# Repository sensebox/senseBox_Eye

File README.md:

# senseBox Eye
## /examples
Some basic examples to test functionality of the MCU. If youre interested in the AI capabilities of the board you can check out this [image classifier](https://github.com/PaulaScharf/senseBox_Eye-edge_impulse) that I created using edge-impulse.

## /hardware
Contains datasheets and schematics.

## /BSP
Contains configuration for the board support package (which have to be included into the [Arduino core for the ESP32](https://github.com/espressif/arduino-esp32)), UF2 bootloader and circuit python bootloader.

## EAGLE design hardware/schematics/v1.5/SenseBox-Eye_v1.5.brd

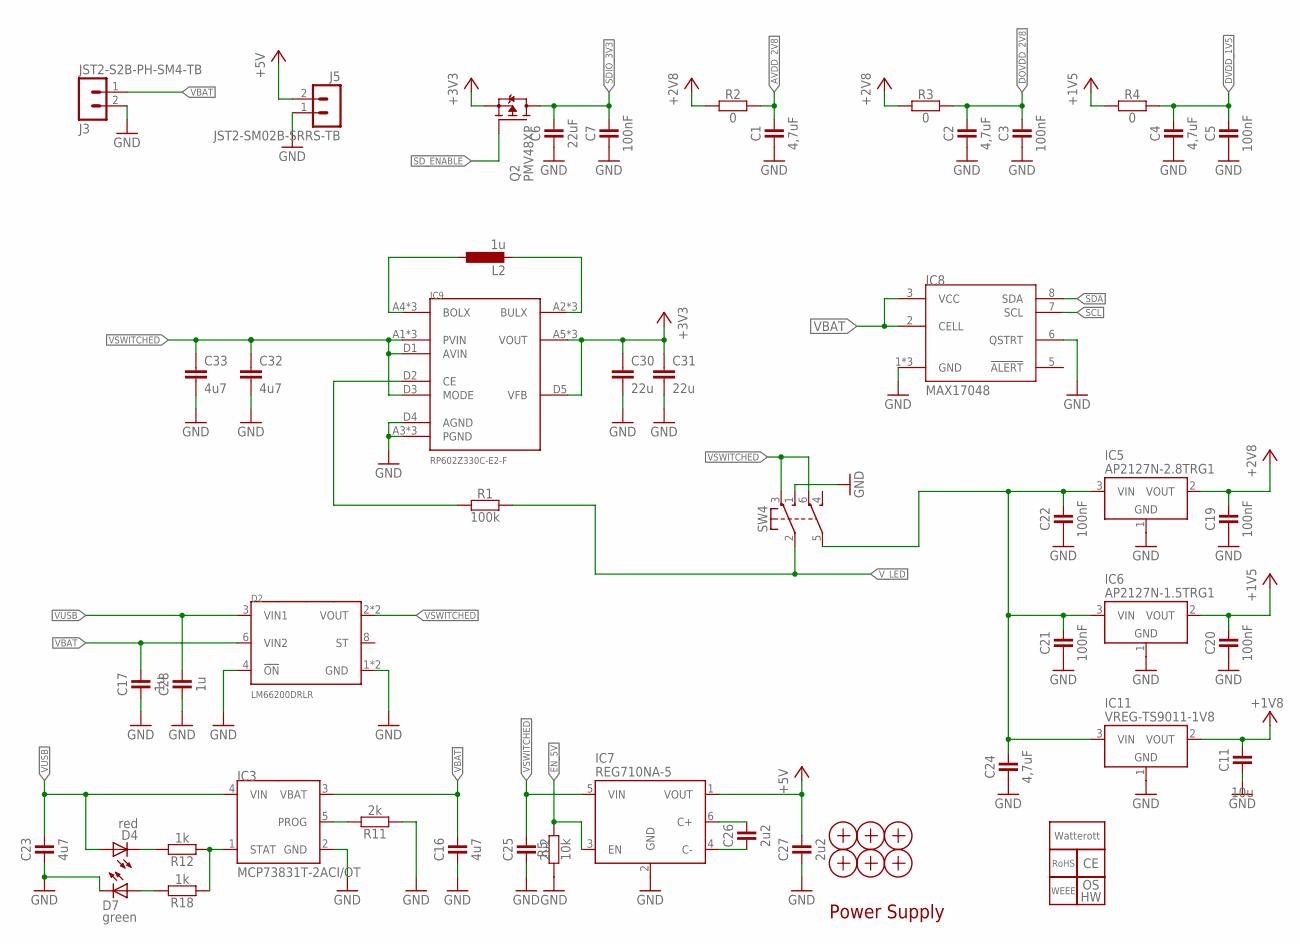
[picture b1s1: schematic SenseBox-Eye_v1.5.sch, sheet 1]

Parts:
C1, C2, C4, C24: 4,7uF; C0402
C3, C5, C7, C19, C20, C21, C22: 100nF; C0402
C6: 22uF; C0402
C11: 10u; C0402
C16, C23: 4u7; C0402
C17, C28: 1u; C0402
C25, C26, C27: 2u2; C0402
C30, C31: 22u; 0805N
C32, C33: 4u7; 0603N
D2: LM66200DRLR; SOT-5X3
D4: red; 0603N
D7: green; 0603N
IC3: MCP73831T-2ACI/OT; SOT23-5
IC5: AP2127N-2.8TRG1; SOT23
IC6: AP2127N-1.5TRG1; SOT23
IC7: REG710NA-5; SOT23-6
IC8: MAX17048; UDFN8_2020
IC9: RP602Z330C-E2-F; WLCSP-20-P1
IC11: VREG-TS9011-1V8; SOT23
J3: JST2-S2B-PH-SM4-TB; JST_S2B-PH-SM4-TB
J5: JST2-SM02B-SRRS-TB; JST_SM02B-SRSS-TB
L2: 1u; 5040
LOGO2: LOGO_CE-5; CE_5MM
LOGO3: LOGO_OSHW-2; OSHW_2MM
LOGO4: LOGO_ROHS-2; ROHS_2MM
LOGO5: LOGO_WEEE-4; WEEE_4MM
LOGO6: LOGO_SPARK-2; SPARK_2MM
Q2: PMV48XP; SOT23
R1: 100k; C0402
R2, R3, R4: 0; C0402
R5: 10k; C0402
R11: 2k; C0402
R12, R18: 1k; C0402
SW4: SW-2UM-CUS22B; CUS22B
X1, X2, X3, X4, X5, X6: PASSER-04; PASSER_04MM

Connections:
+1V5: C20.2, IC6.2 (VOUT), R4.1
+1V8: C11.2, IC11.2 (VOUT); also elsewhere on the board
+2V8: C19.2, IC5.2 (VOUT), R2.1, R3.1
+3V3: C30.1, C31.1, IC9.A5 (VOUT), IC9.B5 (VOUT), IC9.C5 (VOUT), IC9.D5 (VFB), Q2.2 (S); also elsewhere on the board
+5V: C27.2, IC7.1 (VOUT), J5.2
AVDD_2V8: C1.2, R2.2; also elsewhere on the board
BOLX: IC9.A4 (BOLX), IC9.B4 (BOLX), IC9.C4 (BOLX), L2.1
BULX: IC9.A2 (BULX), IC9.B2 (BULX), IC9.C2 (BULX), L2.2
DOVDD_2V8: C2.2, C3.2, R3.2; also elsewhere on the board
DVDD_1V5: C4.2, C5.2, R4.2; also elsewhere on the board
ENABLE_3V3: IC9.D2 (CE), R1.1
EN_5V: IC7.3 (EN), R5.2; also elsewhere on the board
GND: C1.1, C2.1, C3.1, C4.1, C5.1, C6.1, C7.1, C11.1, C16.1, C17.1, C19.1, C20.1, C21.1, C22.1, C23.1, C24.1, C25.1, C27.1, C28.1, C30.2, C31.2, C32.2, C33.2, D2.1 (GND), D2.4 (!ON), D2.5 (GND), D7.C, IC3.2 (GND), IC5.1 (GND), IC6.1 (GND), IC7.2 (GND), IC8.1 (GND), IC8.4 (GND), IC8.6 (QSTRT), IC8.TP (GND), IC9.A3 (PGND), IC9.B3 (PGND), IC9.C3 (PGND), IC9.D4 (AGND), IC11.1 (GND), J3.2, J5.1, R5.1, R11.1, SW4.1 (NO1); also elsewhere on the board
unnamed: C26.2, IC7.6 (C+)
unnamed: C26.1, IC7.4 (C-)
unnamed: D7.A, R18.2
unnamed: D4.C, R12.2
unnamed: IC3.1 (STAT), R12.1, R18.1
unnamed: IC3.5 (PROG), R11.2
SCL: IC8.7 (SCL); also elsewhere on the board
SDA: IC8.8 (SDA); also elsewhere on the board
SDIO_3V3: C6.2, C7.2, Q2.3 (D); also elsewhere on the board
SD_ENABLE: Q2.1 (G); also elsewhere on the board
VBAT: C16.2, C17.2, D2.6 (VIN2), IC3.3 (VBAT), IC8.2 (CELL), IC8.3 (VCC), J3.1
VIN: C21.2, C22.2, C24.2, IC5.3 (VIN), IC6.3 (VIN), IC11.3 (VIN), SW4.5 (C2)
VSWITCHED: C25.2, C32.1, C33.1, D2.2 (VOUT), D2.7 (VOUT), IC7.5 (VIN), IC9.A1 (PVIN), IC9.B1 (PVIN), IC9.C1 (PVIN), IC9.D1 (AVIN), IC9.D3 (MODE), SW4.3 (NC1), SW4.6 (NC2)
VUSB: C23.2, C28.2, D2.3 (VIN1), D4.A, IC3.4 (VIN); also elsewhere on the board
V_LED: R1.2, SW4.2 (C1); also elsewhere on the board

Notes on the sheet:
Power Supply

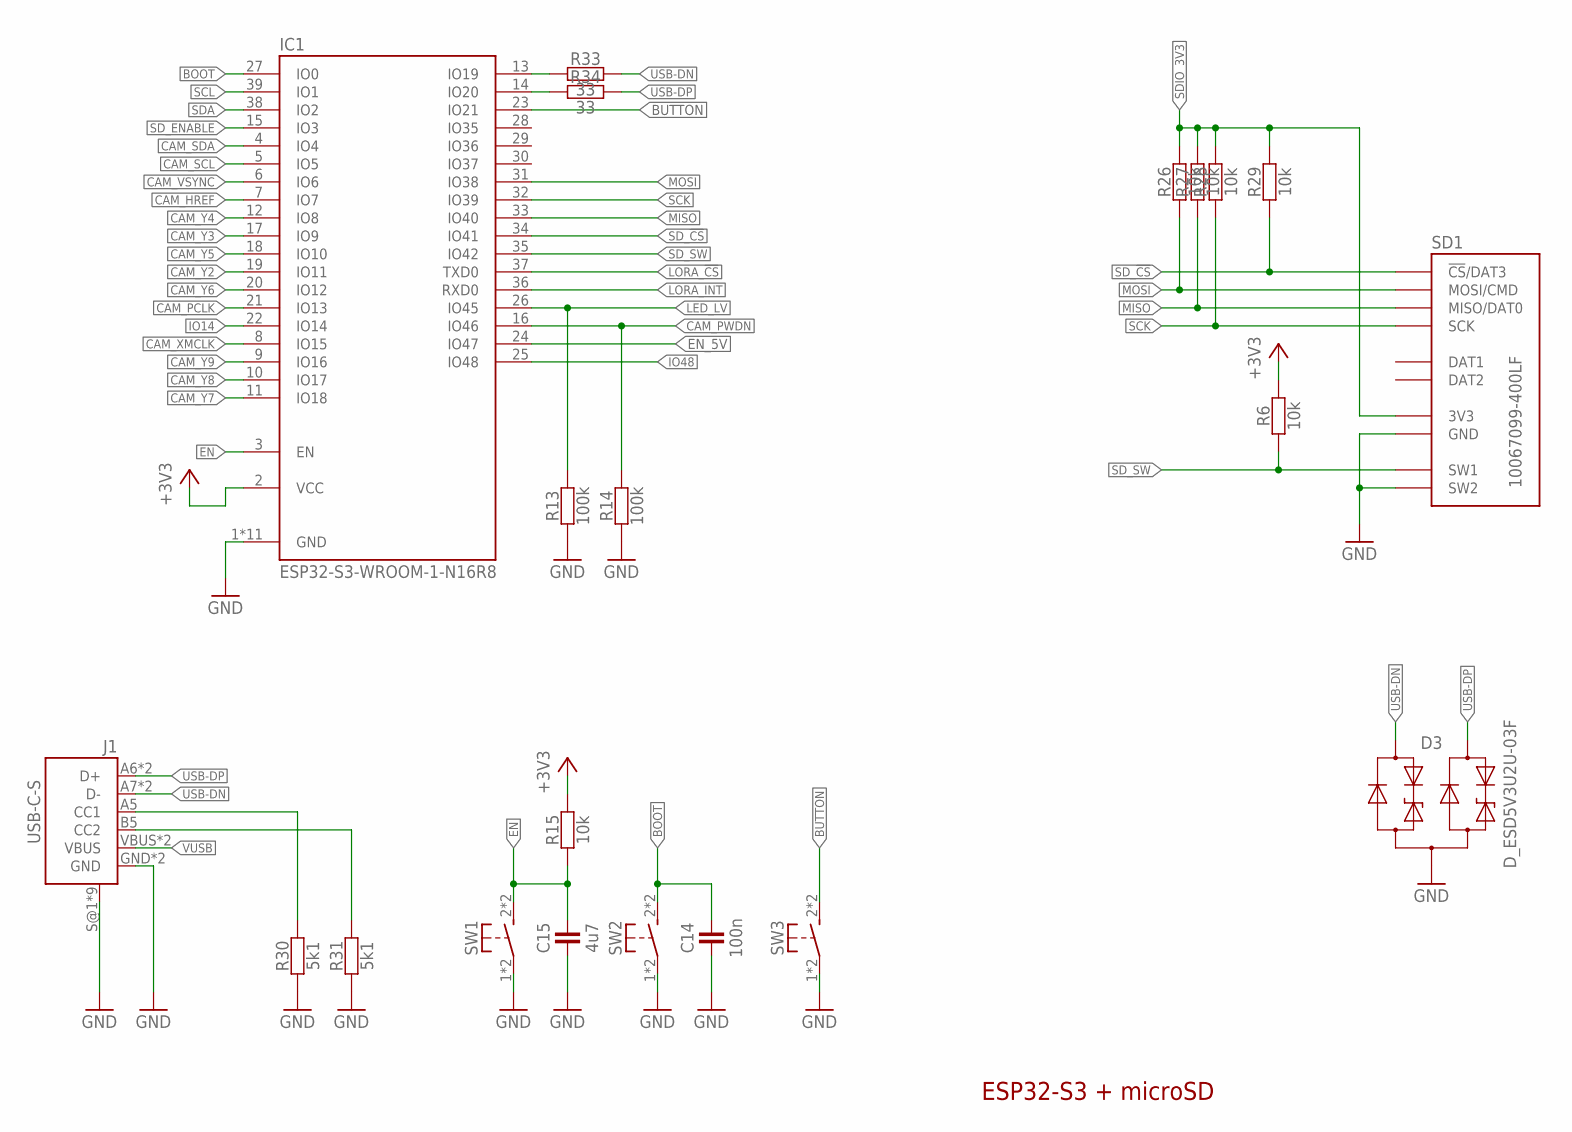
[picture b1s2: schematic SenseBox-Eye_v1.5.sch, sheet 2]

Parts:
C14: 100n; C0402
C15: 4u7; C0402
D3: D_ESD5V3U2U-03F; SOT723
IC1: ESP32-S3-WROOM-1-N16R8; ESP32-S3-WROOM-1
J1: USB-C-S
R6, R15, R26, R27, R28, R29: 10k; C0402
R13, R14: 100k; C0402
R30, R31: 5k1; C0402
R33, R34: 33; C0402
SD1: 10067099-400LF; SD_47309XXXX
SW1, SW2, SW3: SW-TACTILE-TL3305; TL3305

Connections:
+3V3: IC1.2 (VCC), R6.2, R15.2; also elsewhere on the board
BOOT: C14.2, IC1.27 (IO0), SW2.2 (S1), SW2.3 (S1)
BUTTON: IC1.23 (IO21), SW3.2 (S1), SW3.3 (S1)
CAM_HREF: IC1.7 (IO7); also elsewhere on the board
CAM_PCLK: IC1.21 (IO13); also elsewhere on the board
CAM_PWDN: IC1.16 (IO46), R14.2; also elsewhere on the board
CAM_SCL: IC1.5 (IO5); also elsewhere on the board
CAM_SDA: IC1.4 (IO4); also elsewhere on the board
CAM_VSYNC: IC1.6 (IO6); also elsewhere on the board
CAM_XMCLK: IC1.8 (IO15); also elsewhere on the board
CAM_Y2: IC1.19 (IO11); also elsewhere on the board
CAM_Y3: IC1.17 (IO9); also elsewhere on the board
CAM_Y4: IC1.12 (IO8); also elsewhere on the board
CAM_Y5: IC1.18 (IO10); also elsewhere on the board
CAM_Y6: IC1.20 (IO12); also elsewhere on the board
CAM_Y7: IC1.11 (IO18); also elsewhere on the board
CAM_Y8: IC1.10 (IO17); also elsewhere on the board
CAM_Y9: IC1.9 (IO16); also elsewhere on the board
CC1: J1.A5 (CC1), R30.2
CC2: J1.B5 (CC2), R31.2
EN: C15.2, IC1.3 (EN), R15.1, SW1.2 (S1), SW1.3 (S1)
EN_5V: IC1.24 (IO47); also elsewhere on the board
GND: C14.1, C15.1, D3.3 (A), IC1.1 (GND), IC1.40 (GND), IC1.P$1 (GND), IC1.P$2 (GND), IC1.P$3 (GND), IC1.P$4 (GND), IC1.P$5 (GND), IC1.P$6 (GND), IC1.P$7 (GND), IC1.P$8 (GND), IC1.P$9 (GND), J1.GND, J1.GND2 (GND), J1.S@1 (SHIELD), J1.S@2 (SHIELD), J1.S@3 (SHIELD), J1.S@4 (SHIELD), J1.S@5 (SHIELD), J1.S@6 (SHIELD), J1.S@7 (SHIELD), J1.S@8 (SHIELD), J1.S@9 (SHIELD), R13.1, R14.1, R30.1, R31.1, SD1.GND, SD1.GND@1 (GND), SD1.GND@2 (GND), SD1.SW2, SW1.1, SW1.4 (P1), SW2.1, SW2.4 (P1), SW3.1, SW3.4 (P1); also elsewhere on the board
IO14: IC1.22 (IO14); also elsewhere on the board
IO19: IC1.13 (IO19), R33.1
IO20: IC1.14 (IO20), R34.1
IO48: IC1.25 (IO48); also elsewhere on the board
LED_LV: IC1.26 (IO45), R13.2; also elsewhere on the board
LORA_!CS: IC1.37 (TXD0); also elsewhere on the board
LORA_INT: IC1.36 (RXD0); also elsewhere on the board
MISO: IC1.33 (IO40), R27.1, SD1.MISO (MISO/DAT0); also elsewhere on the board
MOSI: IC1.31 (IO38), R26.1, SD1.MOSI (MOSI/CMD); also elsewhere on the board
SCK: IC1.32 (IO39), R28.1, SD1.SCK; also elsewhere on the board
SCL: IC1.39 (IO1); also elsewhere on the board
SDA: IC1.38 (IO2); also elsewhere on the board
SDIO_3V3: R26.2, R27.2, R28.2, R29.2, SD1.VCC (3V3); also elsewhere on the board
SD_!CS: IC1.34 (IO41), R29.1, SD1.CS (!CS!/DAT3)
SD_ENABLE: IC1.15 (IO3); also elsewhere on the board
SD_SW: IC1.35 (IO42), R6.1, SD1.SW1
USB-DN: D3.1 (C1), J1.A7 (D-), J1.B7 (D-), R33.2
USB-DP: D3.2 (C2), J1.A6 (D+), J1.B6 (D+), R34.2
VUSB: J1.VBUS, J1.VBUS2 (VBUS); also elsewhere on the board

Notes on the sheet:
ESP32-S3 + microSD

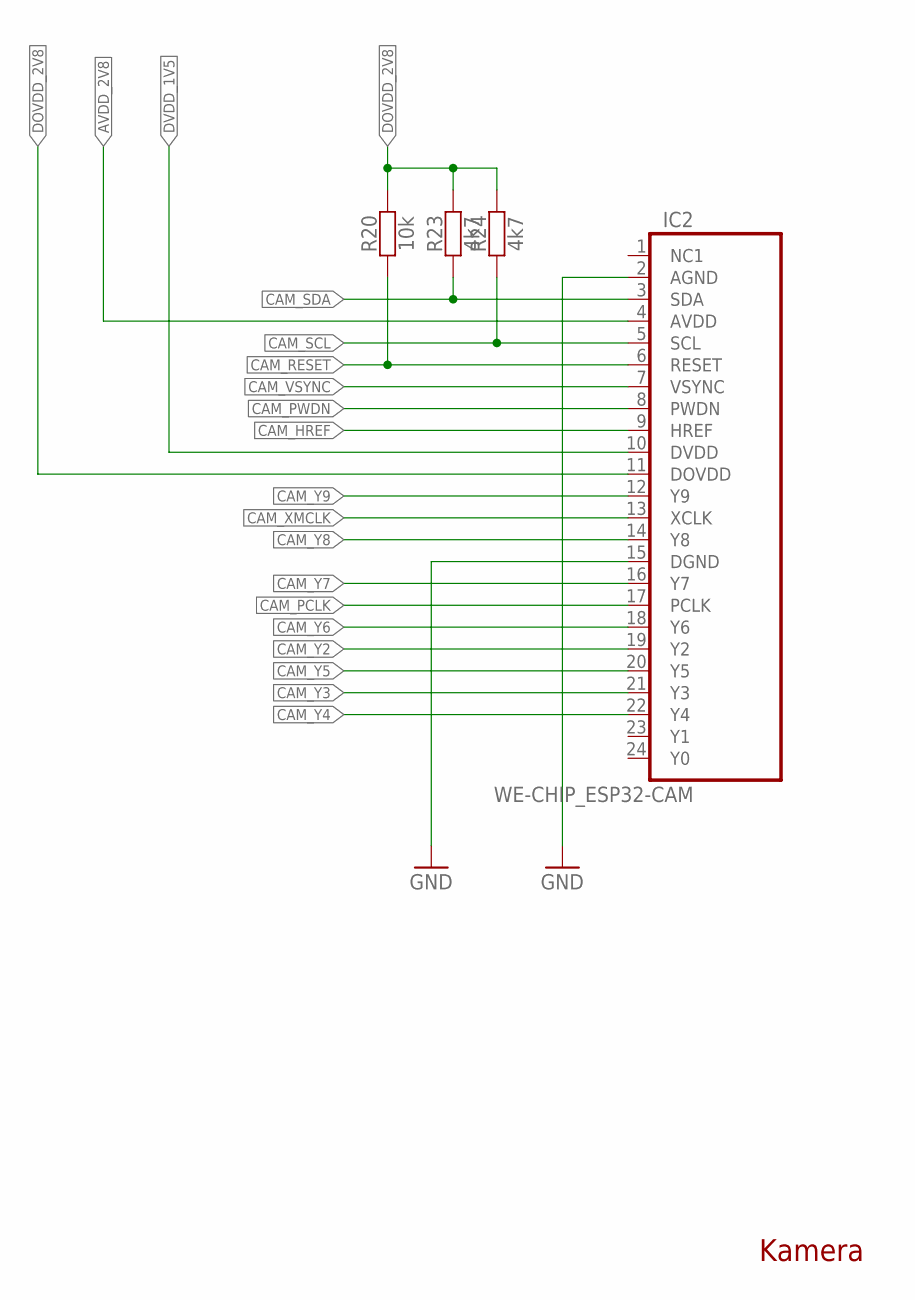
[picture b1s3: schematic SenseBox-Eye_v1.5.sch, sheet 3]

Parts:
IC2: WE-CHIP_ESP32-CAM; WE-CHIP_FPC24-0.5-CAM
R20: 10k; C0402
R23, R24: 4k7; C0402

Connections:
AVDD_2V8: IC2.4 (AVDD); also elsewhere on the board
CAM_HREF: IC2.9 (HREF); also elsewhere on the board
CAM_PCLK: IC2.17 (PCLK); also elsewhere on the board
CAM_PWDN: IC2.8 (PWDN); also elsewhere on the board
CAM_RESET: IC2.6 (RESET), R20.1
CAM_SCL: IC2.5 (SCL), R24.1; also elsewhere on the board
CAM_SDA: IC2.3 (SDA), R23.1; also elsewhere on the board
CAM_VSYNC: IC2.7 (VSYNC); also elsewhere on the board
CAM_XMCLK: IC2.13 (XCLK); also elsewhere on the board
CAM_Y2: IC2.19 (Y2); also elsewhere on the board
CAM_Y3: IC2.21 (Y3); also elsewhere on the board
CAM_Y4: IC2.22 (Y4); also elsewhere on the board
CAM_Y5: IC2.20 (Y5); also elsewhere on the board
CAM_Y6: IC2.18 (Y6); also elsewhere on the board
CAM_Y7: IC2.16 (Y7); also elsewhere on the board
CAM_Y8: IC2.14 (Y8); also elsewhere on the board
CAM_Y9: IC2.12 (Y9); also elsewhere on the board
DOVDD_2V8: IC2.11 (DOVDD), R20.2, R23.2, R24.2; also elsewhere on the board
DVDD_1V5: IC2.10 (DVDD); also elsewhere on the board
GND: IC2.2 (AGND), IC2.15 (DGND); also elsewhere on the board

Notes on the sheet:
Kamera

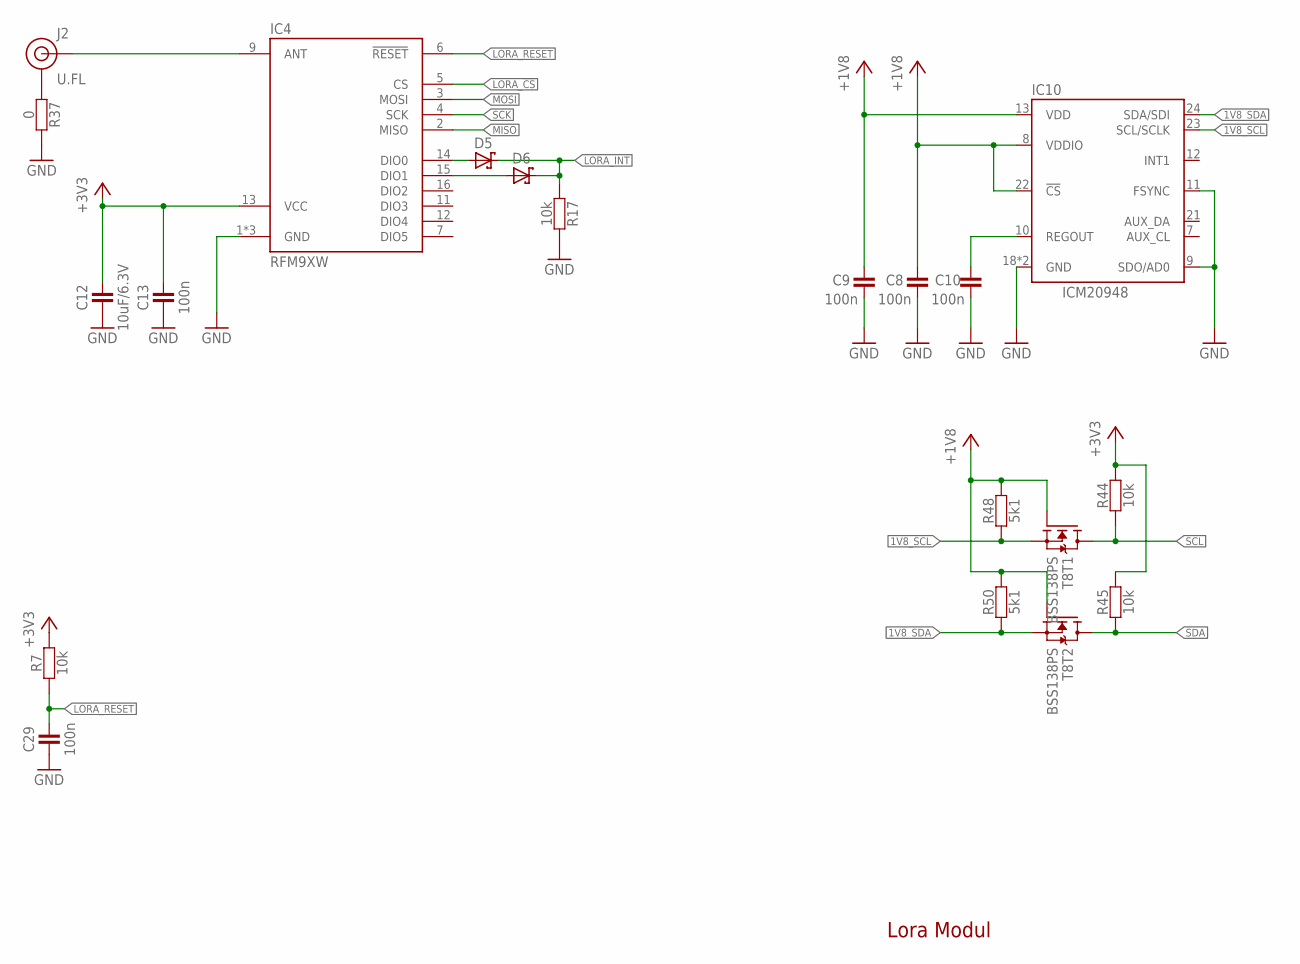
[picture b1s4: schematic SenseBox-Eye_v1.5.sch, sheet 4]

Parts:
C8, C9, C10, C13, C29: 100n; C0402
C12: 10uF/6.3V; C0402
D5, D6: D_SCHOTTKY-SOD523; SOD523
IC4: RFM9XW; RFM9X
IC10: ICM20948; QFN24-3X3
J2: U.FL
R7, R17, R44, R45: 10k; C0402
R37: 0; C0402
R48, R50: 5k1; C0402
T8: BSS138PS; SOT363

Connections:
1V8_SCL: IC10.23 (SCL/SCLK), R48.1, T8.1 (S)
1V8_SDA: IC10.24 (SDA/SDI), R50.1, T8.4 (S)
+1V8: C8.2, C9.2, IC10.8 (VDDIO), IC10.13 (VDD), IC10.22 (!CS), R48.2, R50.2, T8.2 (G), T8.5 (G); also elsewhere on the board
+3V3: C12.2, C13.2, IC4.13 (VCC), R7.2, R44.2, R45.2; also elsewhere on the board
ANT: IC4.9 (ANT), J2.FEED (SIGNAL)
GND: C8.1, C9.1, C10.1, C12.1, C13.1, C29.1, IC4.1 (GND), IC4.8 (GND), IC4.10 (GND), IC10.9 (SDO/AD0), IC10.11 (FSYNC), IC10.18 (GND), IC10.20 (GND), R17.1, R37.1; also elsewhere on the board
LORA_!CS: IC4.5 (CS); also elsewhere on the board
LORA_INT: D5.C, D6.C, R17.2; also elsewhere on the board
LORA_RESET: C29.2, IC4.6 (!RESET), R7.1
MISO: IC4.2 (MISO); also elsewhere on the board
MOSI: IC4.3 (MOSI); also elsewhere on the board
unnamed: D5.A, IC4.14 (DIO0)
unnamed: D6.A, IC4.15 (DIO1)
unnamed: J2.1 (GND), J2.2 (GND), R37.2
REGOUT1: C10.2, IC10.10 (REGOUT)
SCK: IC4.4 (SCK); also elsewhere on the board
SCL: R44.1, T8.6 (D); also elsewhere on the board
SDA: R45.1, T8.3 (D); also elsewhere on the board

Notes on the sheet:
Lora Modul

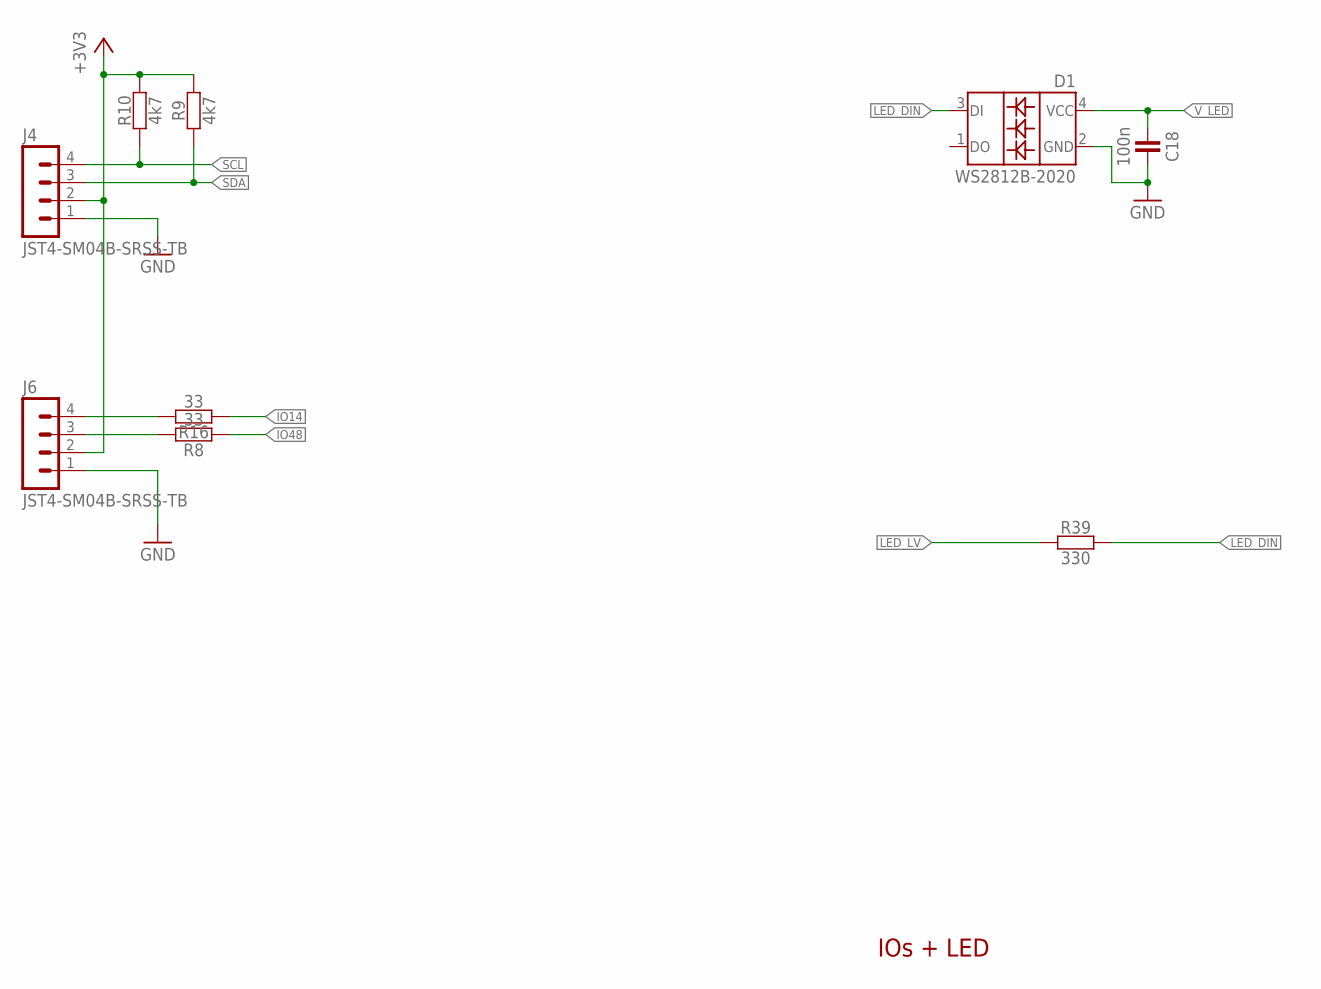
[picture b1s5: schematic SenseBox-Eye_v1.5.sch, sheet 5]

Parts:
C18: 100n; C0402
D1: WS2812B-2020; WS2812_2020
J4, J6: JST4-SM04B-SRSS-TB; JST_SM04B-SRSS-TB
R8, R16: 33; C0402
R9, R10: 4k7; C0402
R39: 330; C0402

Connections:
+3V3: J4.2, J6.2, R9.1, R10.1; also elsewhere on the board
GND: C18.1, D1.2 (GND), J4.1, J6.1; also elsewhere on the board
IO14: R16.2; also elsewhere on the board
IO48: R8.2; also elsewhere on the board
LED_DIN: D1.3 (DI), R39.2
LED_LV: R39.1; also elsewhere on the board
unnamed: J6.4, R16.1
unnamed: J6.3, R8.1
SCL: J4.4, R10.2; also elsewhere on the board
SDA: J4.3, R9.2; also elsewhere on the board
V_LED: C18.2, D1.4 (VCC); also elsewhere on the board

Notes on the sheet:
IOs + LED

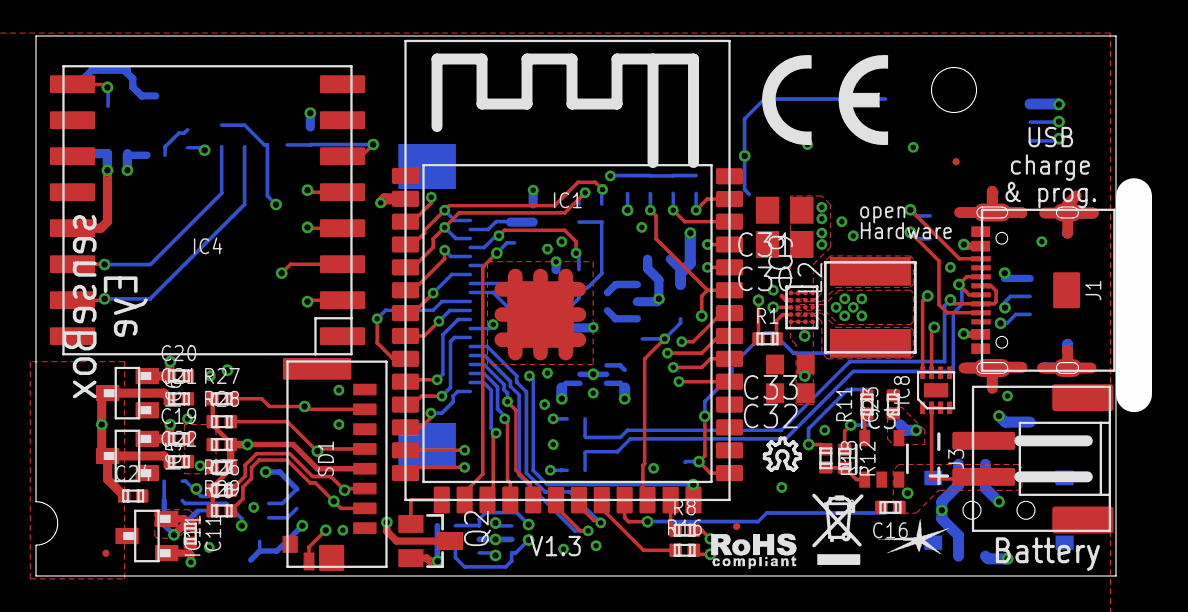
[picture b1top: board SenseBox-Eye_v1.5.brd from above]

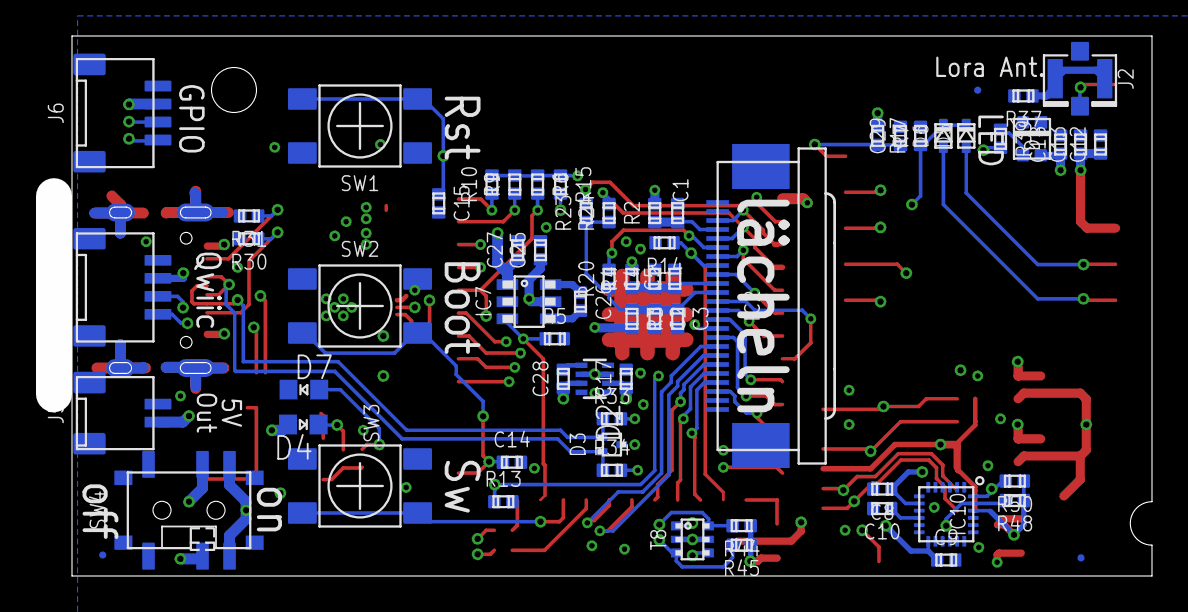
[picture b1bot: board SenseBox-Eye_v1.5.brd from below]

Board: 4 copper layers, 60.0 x 28.0 mm, 111 parts (66 on the bottom side), 74 nets.

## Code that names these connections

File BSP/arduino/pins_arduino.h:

#ifndef Pins_Arduino_h
#define Pins_Arduino_h

#include <stdint.h>

#define USB_VID          0x303A
#define USB_PID          0x82D1
#define USB_MANUFACTURER "senseBox"
#define USB_PRODUCT      "Eye"
#define USB_SERIAL       ""  // Empty string for MAC address

// Default USB FirmwareMSC Settings
#define USB_FW_MSC_VENDOR_ID        "senseBox"     // max 8 chars
#define USB_FW_MSC_PRODUCT_ID       "Eye"  // max 16 chars
#define USB_FW_MSC_PRODUCT_REVISION "1.4"      // max 4 chars
#define USB_FW_MSC_VOLUME_NAME      "senseBox_Eye"     // max 11 chars
#define USB_FW_MSC_SERIAL_NUMBER    0x00000000

#define PIN_RGB_LED 45  // RGB LED
#define RGBLED_PIN  45  // RGB LED
#define PIN_LED     45
#define RGBLED_NUM  1  // number of RGB LEDs

static const uint8_t LED_BUILTIN = PIN_RGB_LED;
#define BUILTIN_LED LED_BUILTIN
#define LED_BUILTIN LED_BUILTIN  // allow #ifdef LED_BUILTIN

// =============================================
// I2C (QWIIC)
// =============================================
#define PIN_WIRE_SDA 2
#define PIN_WIRE_SCL 1

static const uint8_t SDA = PIN_WIRE_SDA;
static const uint8_t SCL = PIN_WIRE_SCL;

// =============================================
// SPI
// =============================================
#define PIN_SPI_MOSI 38
#define PIN_SPI_MISO 40
#define PIN_SPI_SCK  39
#define PIN_SPI_SS   41

static const uint8_t MOSI = PIN_SPI_MOSI;
static const uint8_t MISO = PIN_SPI_MISO;
static const uint8_t SCK  = PIN_SPI_SCK;
static const uint8_t SS   = PIN_SPI_SS;


// IO Pins
#define PIN_IO14 14
static const uint8_t A14 = PIN_IO14;  // Analog
static const uint8_t D14 = PIN_IO14;  // Digital
static const uint8_t T14 = PIN_IO14;  // Touch

#define PIN_IO48 48
static const uint8_t A48 = PIN_IO48;  // Analog
static const uint8_t D48 = PIN_IO48;  // Digital
static const uint8_t T48 = PIN_IO48;  // Touch

// Button
#define PIN_BUTTON 21
#define BUTTON 21

// =============================================
// SD Card
// =============================================
// SD shares the SPI bus — CS, detect switch, enable are SD-specific
#define PIN_SD_CS     41
#define PIN_SD_SW     42
#define PIN_SD_ENABLE 3
#define SD_CS    PIN_SD_CS
#define SD_SW    PIN_SD_SW
#define SD_ENABLE PIN_SD_ENABLE

// USB
#define PIN_USB_DM 19 // DM = D Minus
#define PIN_USB_DN 19 // DN = D Negative (same as DM)
#define PIN_USB_DP 20
#define USB_DN PIN_USB_DN
#define USB_DP PIN_USB_DP

// =============================================
// Camera
// =============================================
#define PWDN_GPIO_NUM  46
#define RESET_GPIO_NUM -1
#define XCLK_GPIO_NUM  15
#define SIOD_GPIO_NUM  4
#define SIOC_GPIO_NUM  5
#define Y9_GPIO_NUM    16
#define Y8_GPIO_NUM    17
#define Y7_GPIO_NUM    18
#define Y6_GPIO_NUM    12
#define Y5_GPIO_NUM    10
#define Y4_GPIO_NUM    8
#define Y3_GPIO_NUM    9
#define Y2_GPIO_NUM    11
#define VSYNC_GPIO_NUM 6
#define HREF_GPIO_NUM  7
#define PCLK_GPIO_NUM  13

// Schematics
#define CAM_PWDN  46
#define CAM_RESET -1
#define CAM_XMCLK   15
#define CAM_SDA    4
#define CAM_SCL    5
#define CAM_Y9     16
#define CAM_Y8     17
#define CAM_Y7     18
#define CAM_Y6     12
#define CAM_Y5     10
#define CAM_Y4     8
#define CAM_Y3     9
#define CAM_Y2     11
#define CAM_VSYNC  6
#define CAM_HREF   7
#define CAM_PCLK   13

    
// =============================================
// LoRa
// =============================================
#define PIN_LORA_CS 43
#define PIN_LORA_INT 44
#define LORA_CS    PIN_LORA_CS
#define LORA_INT   PIN_LORA_INT

#endif /* Pins_Arduino_h */

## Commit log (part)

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2025-03-24 add schematics
2025-03-24 add camerawebserver example
2025-03-24 i2c-scanner and vl53l8cx example
2025-03-24 fix pins
2025-03-24 update example READMEs
2025-03-24 some refactoring
2025-03-24 processor datasheet
2025-03-25 add lora and refactor
2025-03-25 add rainbow cycle example
2025-03-25 add display example
2025-03-25 add Serial example
2025-03-25 add brd and sch
2025-03-25 add button example
2025-03-25 add camera-display example
2025-03-25 add hdc1080 and mpu6050 example
2025-03-25 add sps30 example
2025-03-26 add i2c chain example
2025-03-26 add boot button example
2025-03-26 remove comment
2025-03-26 add mark-ups for BSP
2025-03-26 add qwiic interfaces
2025-03-27 add wifi example
2025-03-27 add alternative pin name
2025-03-28 update name
2025-03-28 update PIDs
2025-03-28 add variant.cpp
2025-03-28 add analog example
2025-03-31 add ble example
2025-03-31 add smt50 example
2025-03-31 basic at command example
2025-04-01 add sd-card example
2025-04-01 update sd-card pins
2025-04-01 add led-matrix example
2025-04-02 add camera sd-card example
2025-04-07 rename
2025-04-07 some sleep examples
2025-04-07 add ttn example
2025-04-08 add v1.1 schematics and rename
2025-04-08 add wifi connect example
2025-04-08 dont limit retries
2025-04-08 mention antenna
2025-04-08 handle disconnects and use sensebox:bike uuids
2025-04-08 update sensebox:bike service uuid
2025-04-08 simplify wifi example
2025-04-08 update antenna info
2025-04-10 add comment about ov7725
2025-04-10 add tested cameras
2025-04-14 add ov7725 example
2025-04-14 surpress error messages when switching camera profile
2025-04-16 add lora abp example
2025-04-16 16mb flash instead of 8
2025-04-16 add platformion and tinyuf2
2025-04-24 update name and flash size
2025-04-29 new schematics
2025-04-29 update v1.2 schematics
2025-05-12 add ref to arduino-esp32 core fix
2025-05-15 add OV5640 example
2025-05-15 add readme about ov5640 and esp32-camera driver
2025-05-22 ref camera settings tutorial
2025-05-26 add CameraWebServer with edge impulse
2025-05-27 refactor
2025-06-04 add esp-idf example
2025-06-04 more details
2025-06-11 warm up camera before actual capture
2025-06-11 update RGB_LED pin
2025-06-11 update GPIO pins
2025-06-11 add vl53l8cx + LED-matrix example
2025-06-11 add max17048
2025-06-23 update camera pins
2025-07-03 update BSP pins
2025-07-10 check if sd card inserted with SW Pin
2025-07-10 update led pin
2025-07-10 use custom partition and enable psram
2025-08-26 all pages
2025-11-20 add multiplexer example
2026-02-03 add openSenseMap example
2026-03-04 update new lora module
2026-03-05 add acceleration sensor examples
2026-03-09 update bsp files and add radiolib lora example for sx1276 chip
2026-03-10 relocate example, readme, library version
2026-03-10 rename lora pins
2026-03-10 add scale example
2026-03-10 update BSP
2026-03-10 refactor and update readme
2026-03-16 add 5V-out example
2026-04-20 add Datenblatt draft
2026-06-16 update button pin in examples
2026-06-16 fix led-matrix sketch
2026-06-16 update cameraWebServer example
2026-06-16 update 5V pin
2026-06-17 update pins in BSP
2026-06-22 update Datenblatt
